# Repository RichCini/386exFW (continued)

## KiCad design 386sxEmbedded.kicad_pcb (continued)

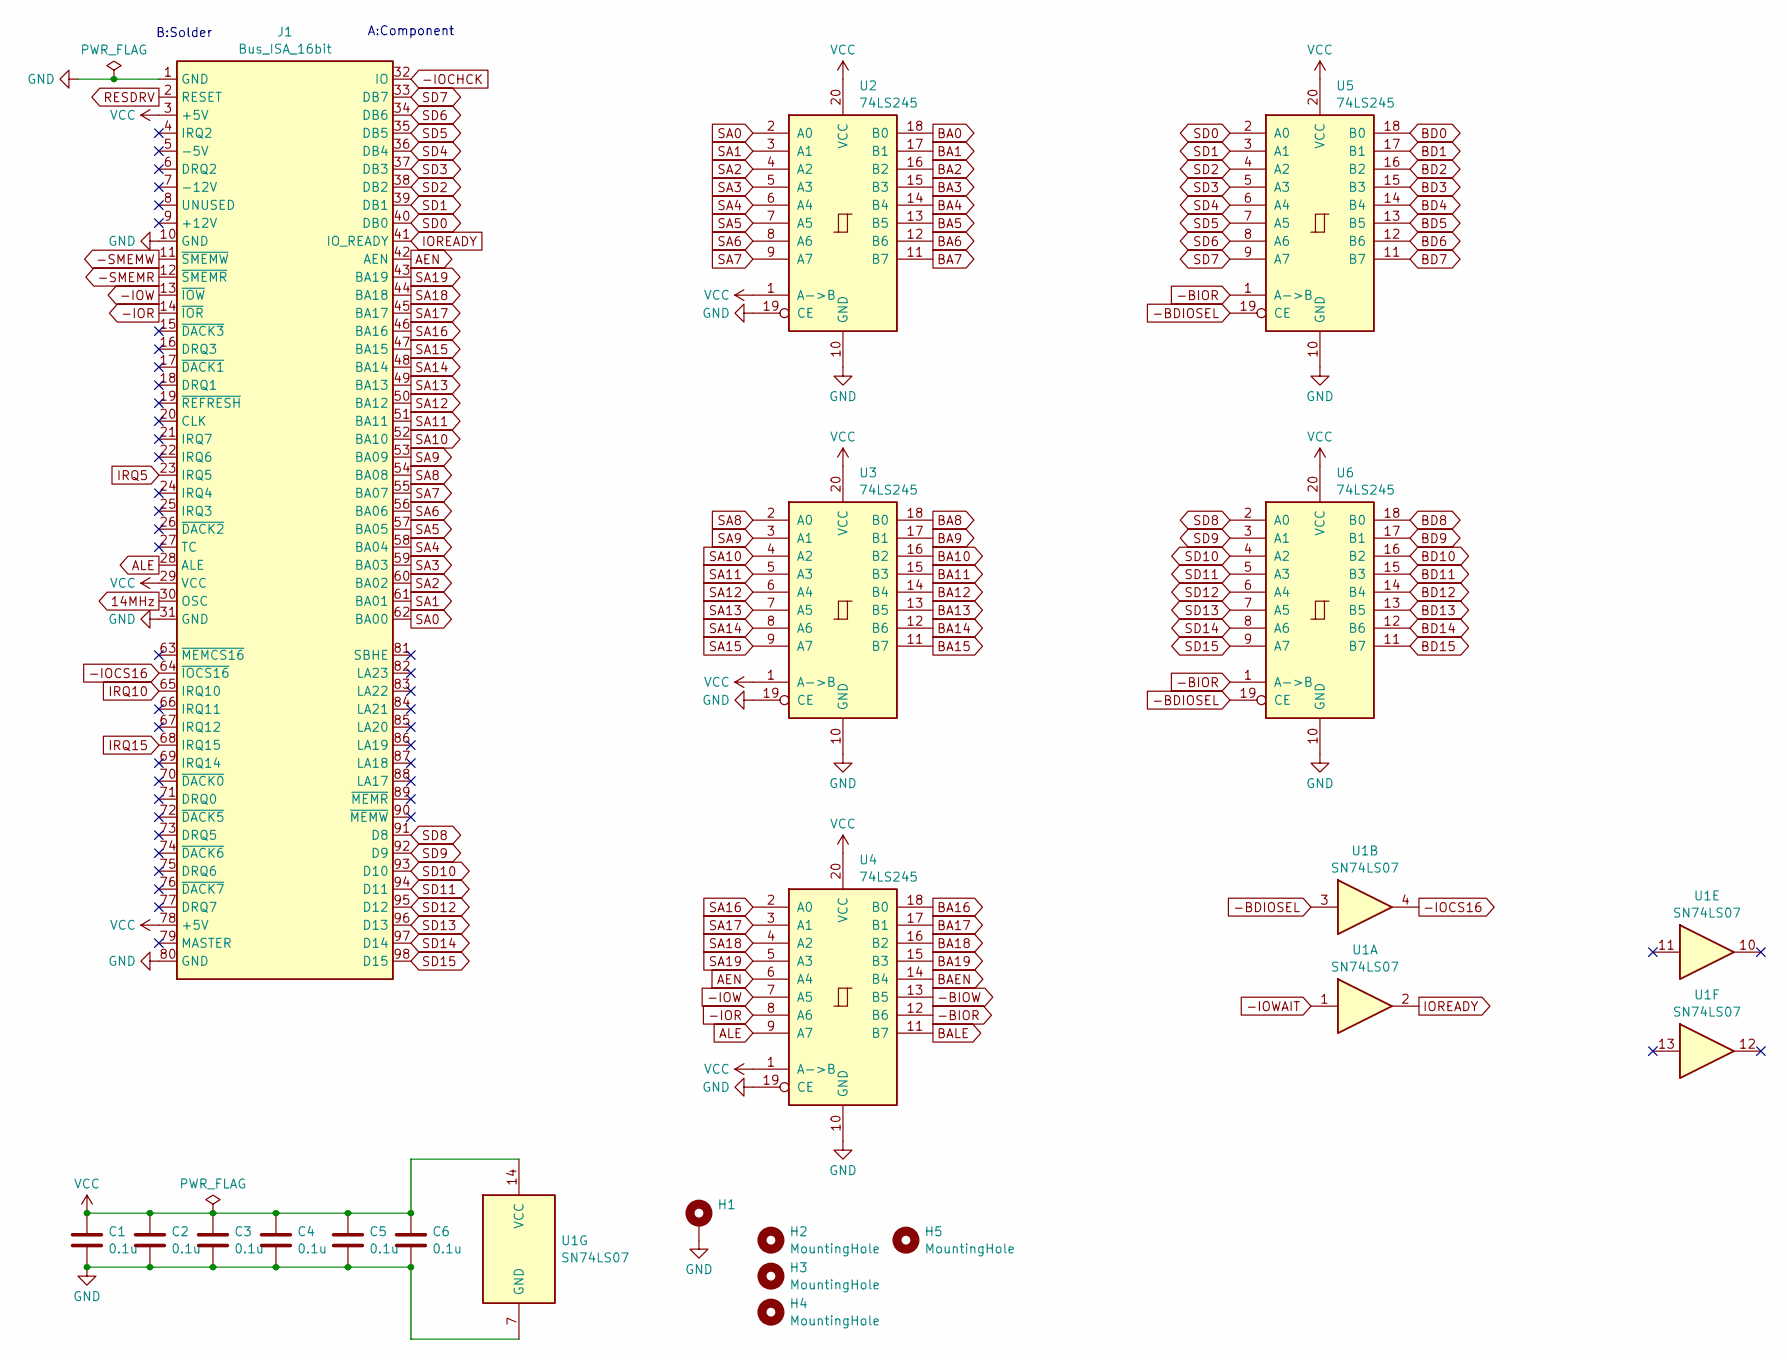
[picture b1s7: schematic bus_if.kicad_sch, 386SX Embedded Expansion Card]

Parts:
C1, C2, C3, C4, C5, C6: 0.1u; C_Disc_D4.3mm_W1.9mm_P5.00mm
H1: MountingHole_Pad; MountingHole_3.2mm_M3_Pad
H2, H3, H4, H5: MountingHole; MountingHole_3.2mm_M3
J1: Bus_ISA_16bit; BUS_AT
U1: SN74LS07; DIP-14_W7.62mm_Socket
U2, U3, U4, U5, U6: 74LS245; DIP-20_W7.62mm_Socket

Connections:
14MHz: J1.30 (OSC); also elsewhere on the board
-BDIOSEL: U1.3, U5.19 (CE), U6.19 (CE); also elsewhere on the board
-BIOR: U4.12 (B6), U5.1 (A->B), U6.1 (A->B); also elsewhere on the board
-BIOW: U4.13 (B5); also elsewhere on the board
-IOCHCK: J1.32 (IO); also elsewhere on the board
-IOCS16: J1.64 (~IOCS16), U1.4
-IOR: J1.14 (~IOR), U4.8 (A6)
-IOW: J1.13 (~IOW), U4.7 (A5)
-IOWAIT: U1.1; also elsewhere on the board
-SMEMR: J1.12 (~SMEMR); also elsewhere on the board
-SMEMW: J1.11 (~SMEMW); also elsewhere on the board
AEN: J1.42 (AEN), U4.6 (A4)
ALE: J1.28 (ALE), U4.9 (A7)
BA0: U2.18 (B0); also elsewhere on the board
BA1: U2.17 (B1); also elsewhere on the board
BA2: U2.16 (B2); also elsewhere on the board
BA3: U2.15 (B3); also elsewhere on the board
BA4: U2.14 (B4); also elsewhere on the board
BA5: U2.13 (B5); also elsewhere on the board
BA6: U2.12 (B6); also elsewhere on the board
BA7: U2.11 (B7); also elsewhere on the board
BA8: U3.18 (B0); also elsewhere on the board
BA9: U3.17 (B1); also elsewhere on the board
BA10: U3.16 (B2); also elsewhere on the board
BA11: U3.15 (B3); also elsewhere on the board
BA12: U3.14 (B4); also elsewhere on the board
BA13: U3.13 (B5); also elsewhere on the board
BA14: U3.12 (B6); also elsewhere on the board
BA15: U3.11 (B7); also elsewhere on the board
BA16: U4.18 (B0); also elsewhere on the board
BA17: U4.17 (B1); also elsewhere on the board
BA18: U4.16 (B2); also elsewhere on the board
BA19: U4.15 (B3); also elsewhere on the board
BAEN: U4.14 (B4); also elsewhere on the board
BALE: U4.11 (B7); also elsewhere on the board
BD0: U5.18 (B0); also elsewhere on the board
BD1: U5.17 (B1); also elsewhere on the board
BD2: U5.16 (B2); also elsewhere on the board
BD3: U5.15 (B3); also elsewhere on the board
BD4: U5.14 (B4); also elsewhere on the board
BD5: U5.13 (B5); also elsewhere on the board
BD6: U5.12 (B6); also elsewhere on the board
BD7: U5.11 (B7); also elsewhere on the board
BD8: U6.18 (B0); also elsewhere on the board
BD9: U6.17 (B1); also elsewhere on the board
BD10: U6.16 (B2); also elsewhere on the board
BD11: U6.15 (B3); also elsewhere on the board
BD12: U6.14 (B4); also elsewhere on the board
BD13: U6.13 (B5); also elsewhere on the board
BD14: U6.12 (B6); also elsewhere on the board
BD15: U6.11 (B7); also elsewhere on the board
GND: C1.2, C2.2, C3.2, C4.2, C5.2, C6.2, H1.1, J1.1 (GND), J1.10 (GND), J1.31 (GND), J1.80 (GND), U1.7 (GND), U2.10 (GND), U2.19 (CE), U3.10 (GND), U3.19 (CE), U4.10 (GND), U4.19 (CE), U5.10 (GND), U6.10 (GND); also elsewhere on the board
IOREADY: J1.41 (IO_READY), U1.2
IRQ5: J1.23 (IRQ5); also elsewhere on the board
IRQ10: J1.65 (IRQ10); also elsewhere on the board
IRQ15: J1.68 (IRQ15); also elsewhere on the board
RESDRV: J1.2 (RESET); also elsewhere on the board
SA0: J1.62 (BA00), U2.2 (A0)
SA1: J1.61 (BA01), U2.3 (A1)
SA2: J1.60 (BA02), U2.4 (A2)
SA3: J1.59 (BA03), U2.5 (A3)
SA4: J1.58 (BA04), U2.6 (A4)
SA5: J1.57 (BA05), U2.7 (A5)
SA6: J1.56 (BA06), U2.8 (A6)
SA7: J1.55 (BA07), U2.9 (A7)
SA8: J1.54 (BA08), U3.2 (A0)
SA9: J1.53 (BA09), U3.3 (A1)
SA10: J1.52 (BA10), U3.4 (A2)
SA11: J1.51 (BA11), U3.5 (A3)
SA12: J1.50 (BA12), U3.6 (A4)
SA13: J1.49 (BA13), U3.7 (A5)
SA14: J1.48 (BA14), U3.8 (A6)
SA15: J1.47 (BA15), U3.9 (A7)
SA16: J1.46 (BA16), U4.2 (A0)
SA17: J1.45 (BA17), U4.3 (A1)
SA18: J1.44 (BA18), U4.4 (A2)
SA19: J1.43 (BA19), U4.5 (A3)
SD0: J1.40 (DB0), U5.2 (A0); also elsewhere on the board
SD1: J1.39 (DB1), U5.3 (A1); also elsewhere on the board
SD2: J1.38 (DB2), U5.4 (A2); also elsewhere on the board
SD3: J1.37 (DB3), U5.5 (A3); also elsewhere on the board
SD4: J1.36 (DB4), U5.6 (A4); also elsewhere on the board
SD5: J1.35 (DB5), U5.7 (A5); also elsewhere on the board
SD6: J1.34 (DB6), U5.8 (A6); also elsewhere on the board
SD7: J1.33 (DB7), U5.9 (A7); also elsewhere on the board
SD8: J1.91 (D8), U6.2 (A0)
SD9: J1.92 (D9), U6.3 (A1)
SD10: J1.93 (D10), U6.4 (A2)
SD11: J1.94 (D11), U6.5 (A3)
SD12: J1.95 (D12), U6.6 (A4)
SD13: J1.96 (D13), U6.7 (A5)
SD14: J1.97 (D14), U6.8 (A6)
SD15: J1.98 (D15), U6.9 (A7)
VCC: C1.1, C2.1, C3.1, C4.1, C5.1, C6.1, J1.3 (+5V), J1.29 (VCC), J1.78 (+5V), U1.14 (VCC), U2.1 (A->B), U2.20 (VCC), U3.1 (A->B), U3.20 (VCC), U4.1 (A->B), U4.20 (VCC), U5.20 (VCC), U6.20 (VCC); also elsewhere on the board

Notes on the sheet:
B:Solder
A:Component

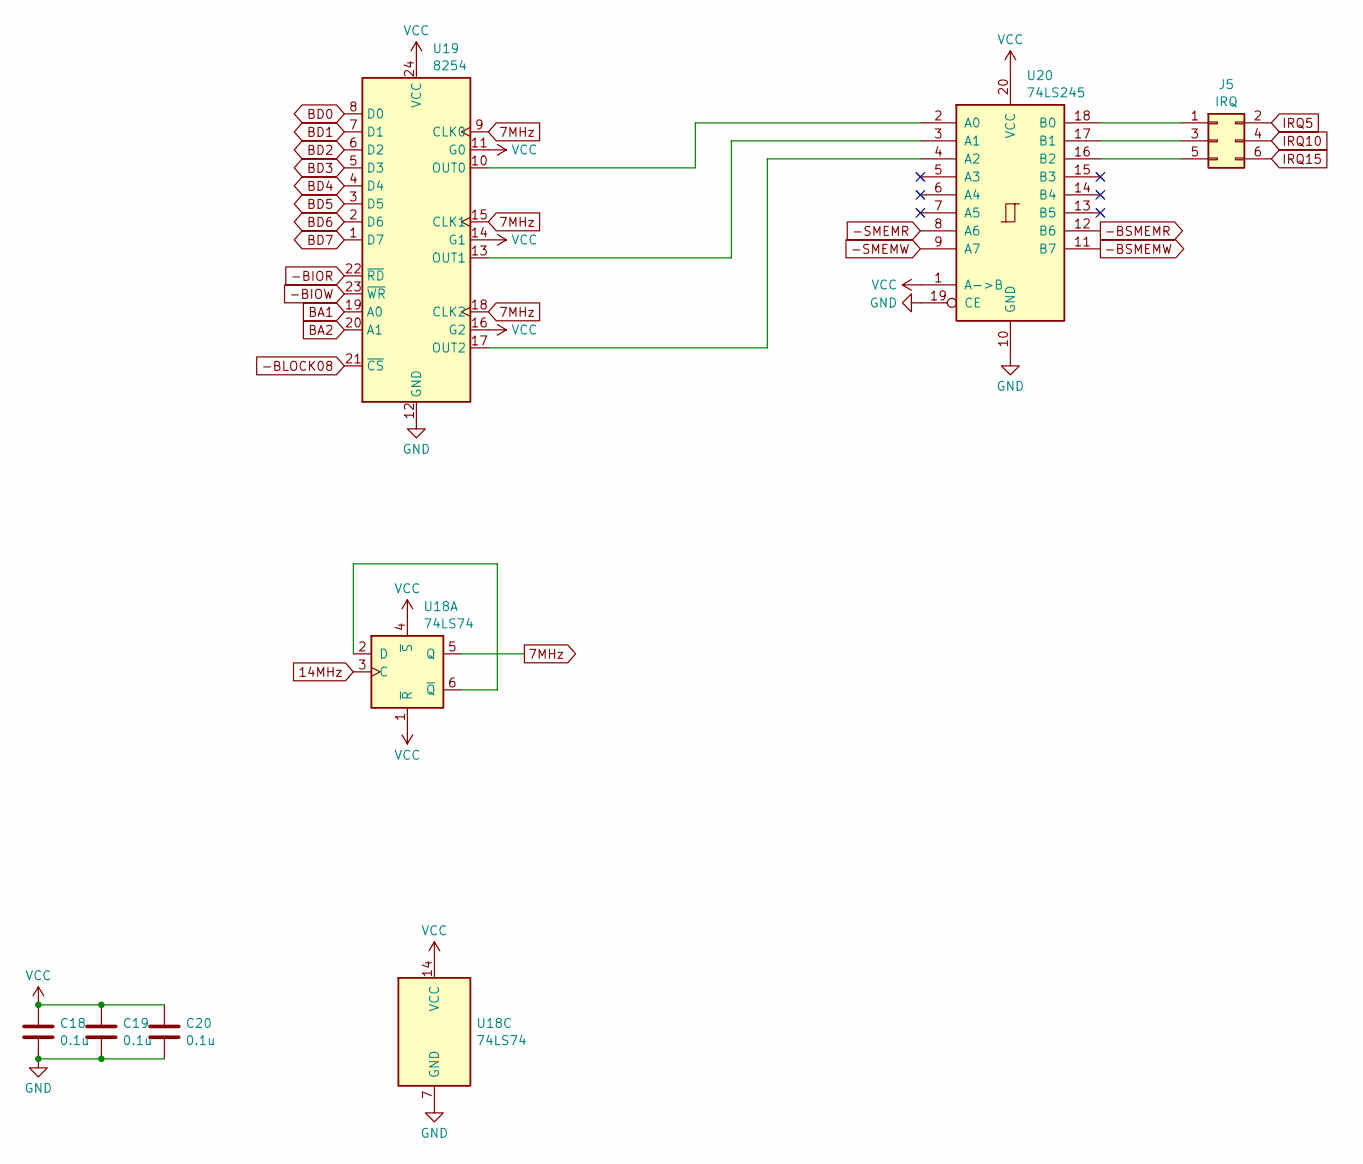
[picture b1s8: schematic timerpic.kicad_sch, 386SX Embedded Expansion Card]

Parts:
C18, C19, C20: 0.1u; C_Disc_D4.3mm_W1.9mm_P5.00mm
J5: IRQ; PinHeader_2x03_P2.54mm_Vertical
U18: 74LS74; DIP-14_W7.62mm_Socket
U19: 8254; DIP-24_W15.24mm
U20: 74LS245; DIP-20_W7.62mm_Socket

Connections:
7MHz: U18.5 (Q), U19.9 (CLK0), U19.15 (CLK1), U19.18 (CLK2)
14MHz: U18.3 (C); also elsewhere on the board
-BIOR: U19.22 (~RD); also elsewhere on the board
-BIOW: U19.23 (~WR); also elsewhere on the board
-BLOCK08: U19.21 (~CS); also elsewhere on the board
-BSMEMR: U20.12 (B6); also elsewhere on the board
-BSMEMW: U20.11 (B7); also elsewhere on the board
-SMEMR: U20.8 (A6); also elsewhere on the board
-SMEMW: U20.9 (A7); also elsewhere on the board
BA1: U19.19 (A0); also elsewhere on the board
BA2: U19.20 (A1); also elsewhere on the board
BD0: U19.8 (D0); also elsewhere on the board
BD1: U19.7 (D1); also elsewhere on the board
BD2: U19.6 (D2); also elsewhere on the board
BD3: U19.5 (D3); also elsewhere on the board
BD4: U19.4 (D4); also elsewhere on the board
BD5: U19.3 (D5); also elsewhere on the board
BD6: U19.2 (D6); also elsewhere on the board
BD7: U19.1 (D7); also elsewhere on the board
GND: C18.2, C19.2, C20.2, U18.7 (GND), U19.12 (GND), U20.10 (GND), U20.19 (CE); also elsewhere on the board
IRQ5: J5.2; also elsewhere on the board
IRQ10: J5.4; also elsewhere on the board
IRQ15: J5.6; also elsewhere on the board
unnamed: J5.1, U20.18 (B0)
unnamed: J5.3, U20.17 (B1)
unnamed: J5.5, U20.16 (B2)
unnamed: U18.2 (D), U18.6 (~Q)
unnamed: U19.10 (OUT0), U20.2 (A0)
unnamed: U19.13 (OUT1), U20.3 (A1)
unnamed: U19.17 (OUT2), U20.4 (A2)
VCC: C18.1, C19.1, C20.1, U18.1 (~R), U18.4 (~S), U18.14 (VCC), U19.11 (G0), U19.14 (G1), U19.16 (G2), U19.24 (VCC), U20.1 (A->B), U20.20 (VCC); also elsewhere on the board

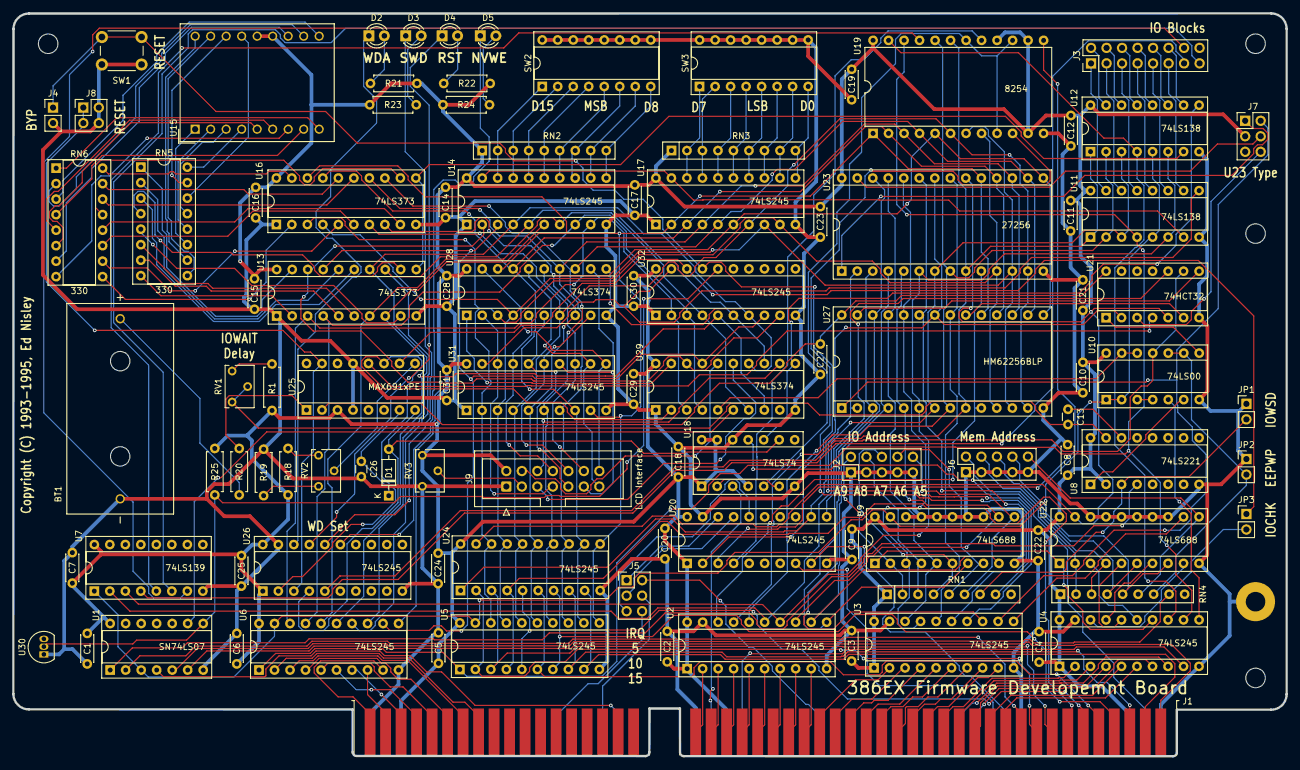
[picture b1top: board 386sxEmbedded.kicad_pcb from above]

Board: 2 copper layers, 208.6 x 121.7 mm, 107 parts (0 on the bottom side), 235 nets.
